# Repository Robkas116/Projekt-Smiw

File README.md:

This is a project of two-part PCB board based on STAMPS3 processor with 
  - RTC DS3231S with battery
  - TP4056 charger connected to USB port
  - Temperature, humidity and CO2 sensor SCD40-D-R1
  - FRAM 8KB memory MB85RS64V
  - Step Up MT3608
  - Step Down AMS1117-3.3

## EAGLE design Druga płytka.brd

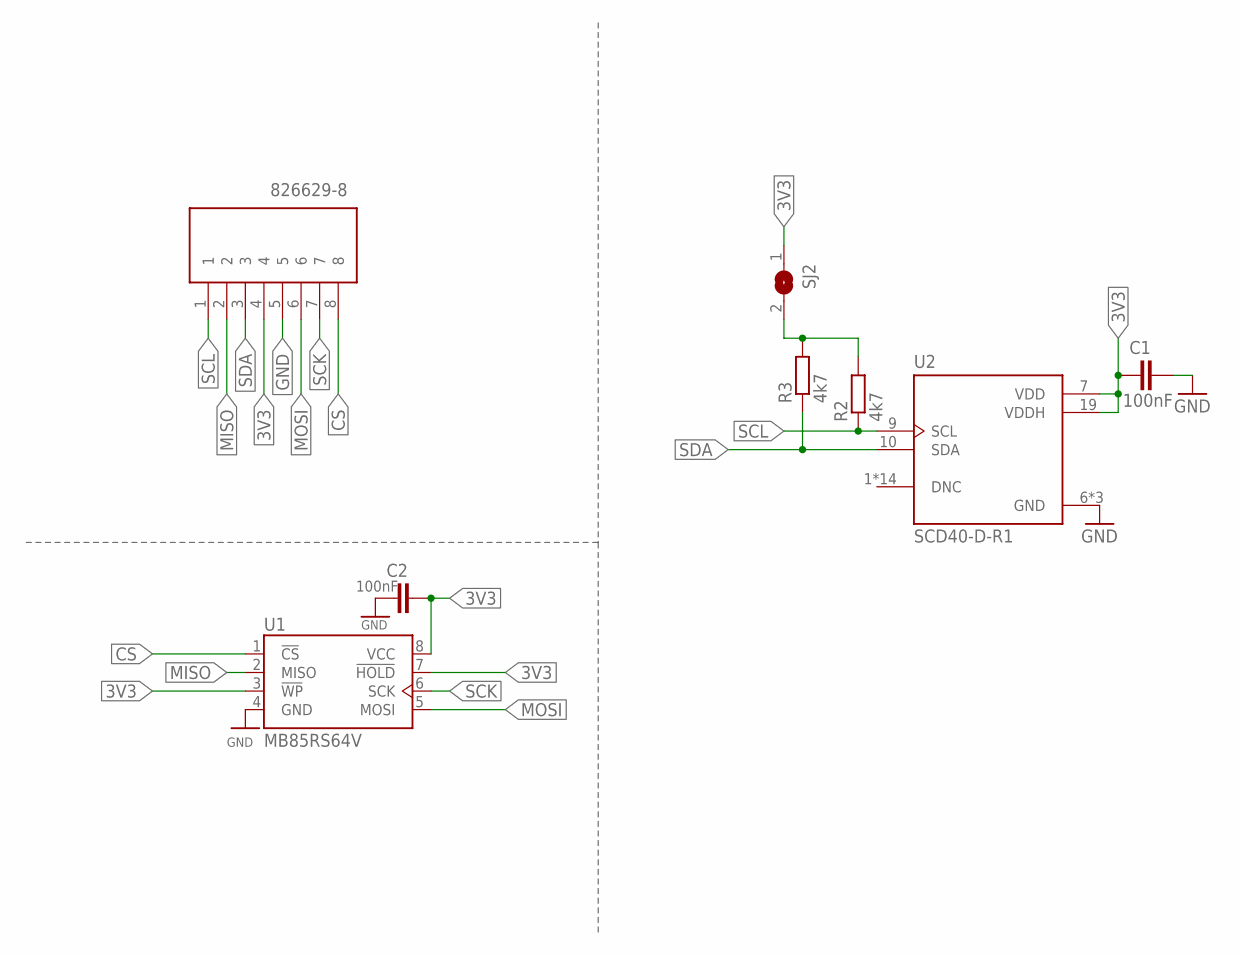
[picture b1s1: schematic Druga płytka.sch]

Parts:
C1, C2: 100nF; C0402
J1: 826629-8; HDRV8W63P0X254_1X8_2032X250X95
R2, R3: 4k7; R1206
SJ2: SJ
U1: MB85RS64V; SOIC127P600X155-8_R159_68_374R15
U2: SCD40-D-R1; XDCR_SCD40-D-R1

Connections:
3V3: C1.2, C2.1, J1.4, SJ2.1, U1.3 (!WP), U1.7 (!HOLD), U1.8 (VCC), U2.7 (VDD), U2.19 (VDDH)
CS: J1.8, U1.1 (!CS)
GND: C1.1, C2.2, J1.5, U1.4 (GND), U2.6 (GND), U2.20 (GND), U2.21 (GND)
JUMPER: R2.2, R3.2, SJ2.2
MISO: J1.2, U1.2 (MISO)
MOSI: J1.6, U1.5 (MOSI)
SCK: J1.7, U1.6 (SCK)
SCL: J1.1, R2.1, U2.9 (SCL)
SDA: J1.3, R3.1, U2.10 (SDA)

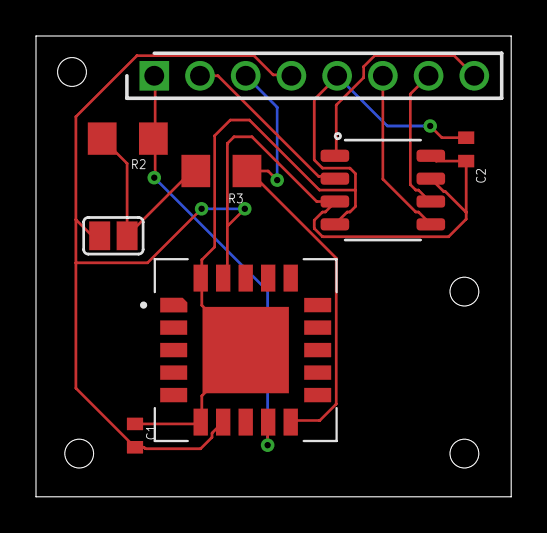
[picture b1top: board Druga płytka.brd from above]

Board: 2 copper layers, 26.4 x 25.6 mm, 8 parts (0 on the bottom side), 9 nets.

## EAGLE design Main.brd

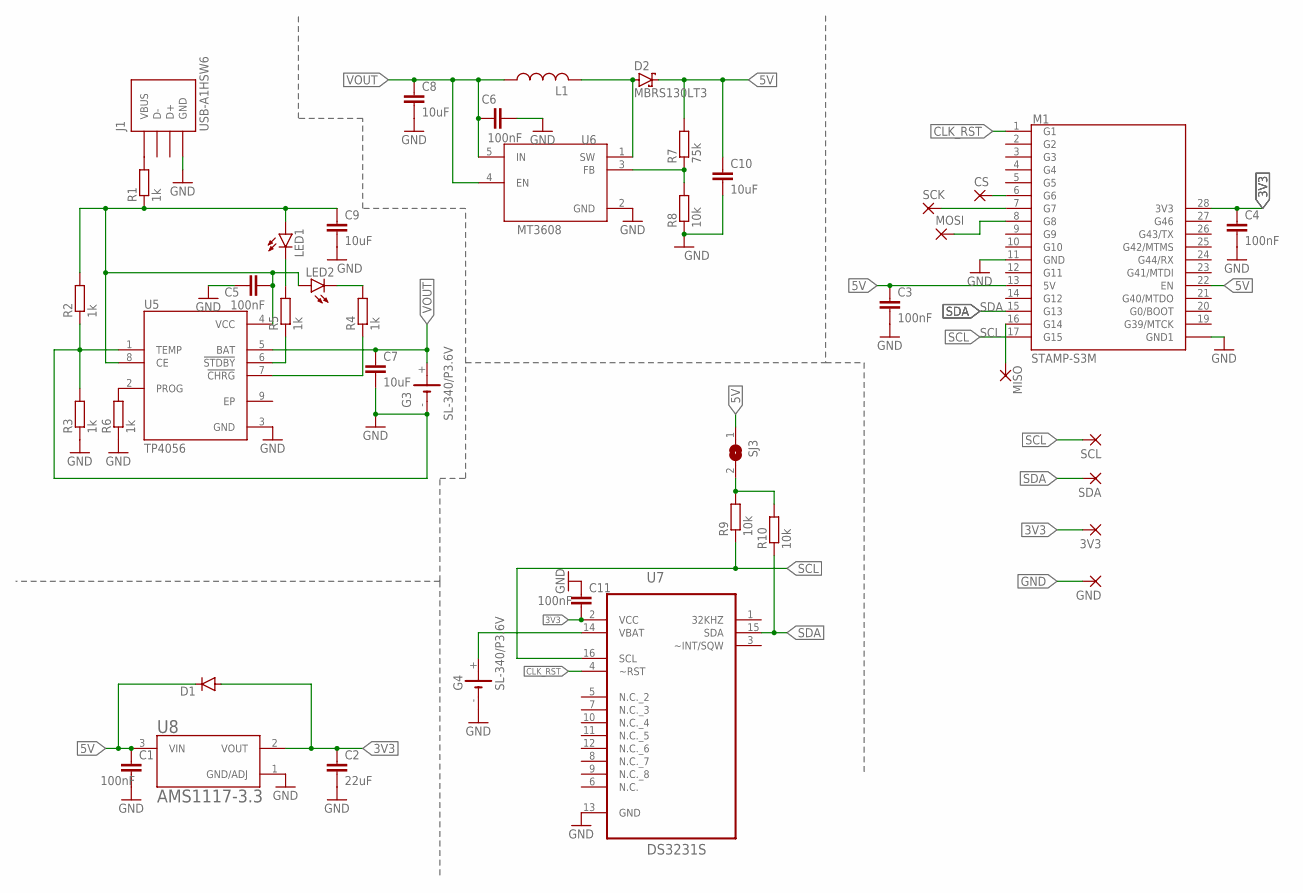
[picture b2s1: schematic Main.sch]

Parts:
3V3: 1,6/0,8
C1, C3, C4, C5, C6, C11: 100nF; C0402
C2: 22uF; C0402
C7, C8, C9, C10: 10uF; C0402
CS: 1,6/0,8
D1: DIODE-SMB; SMB
D2: MBRS130LT3; SMB
G3, G4: SL-340/P3.6V
GND: 1,6/0,8
J1: USB-A1HSW6; OST_USB-A1HSW6
L1: L-USL3225M; L3225M
LED1, LED2: LEDCHIPLED_0805; CHIPLED_0805
MISO: 1,6/0,8
MOSI: 1,6/0,8
R1, R2, R3, R4, R5, R6: 1k; M1206
R7: 75k; M1206
R8, R9, R10: 10k; M1206
SCK: 1,6/0,8
SCL: 1,6/0,8
SDA: 1,6/0,8
SJ3: SJ
U5: TP4056; SOP127P600X175-9N
U6: MT3608; SOT95P280X145-6N
U7: DS3231S; SOIC127P1032X265-16N
U8: AMS1117-3.3; SOT229P700X180-4N
U$1: STAMP-S3M-PIN; STAMPS3_PIN_FTP

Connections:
3V3: 3V3.1, C2.1, C4.1, C11.2, D1.A, U7.2 (VCC), U8.2 (VOUT), U$1.28 (3V3)
5V: C1.1, C3.1, C10.1, D1.C, D2.C, R7.2, SJ3.1, U8.3 (VIN), U$1.13 (5V), U$1.22 (EN)
CHRG: R4.1, U5.7 (!CHRG)
CHRG2: LED2.C, R4.2
CLK_RST: U7.4 (~RST), U$1.1 (G1)
CS: CS.1, U$1.6 (G6)
FB: R7.1, R8.2, U6.3 (FB)
GND: C1.2, C2.2, C3.2, C4.2, C5.1, C6.2, C7.2, C8.2, C9.2, C10.2, C11.1, G3.-, G4.-, GND.1, J1.4 (GND), R2.1, R3.1, R3.2, R6.1, R8.1, U5.1 (TEMP), U5.3 (GND), U6.2 (GND), U7.13 (GND), U8.1 (GND/ADJ), U$1.11 (GND), U$1.18 (GND1)
JUMPER: R9.2, R10.2, SJ3.2
MISO: MISO.1, U$1.16 (G14)
MOSI: MOSI.1, U$1.8 (G8)
unnamed: R6.2, U5.2 (PROG)
unnamed: LED1.C, R5.2
unnamed: J1.1 (VBUS), R1.2
SCK: SCK.1, U$1.7 (G7)
SCL: R9.1, SCL.1, U7.16 (SCL), U$1.17 (G15)
SDA: R10.1, SDA.1, U7.15 (SDA), U$1.15 (G13)
STDBY: R5.1, U5.6 (!STDBY)
SW: D2.A, L1.2, U6.1 (SW)
USB1: C5.2, C9.1, LED1.A, LED2.A, R1.1, R2.2, U5.4 (VCC), U5.8 (CE)
VBAT: G4.+, U7.14 (VBAT)
VOUT: C6.1, C7.1, C8.1, G3.+, L1.1, U5.5 (BAT), U6.4 (EN), U6.5 (IN)

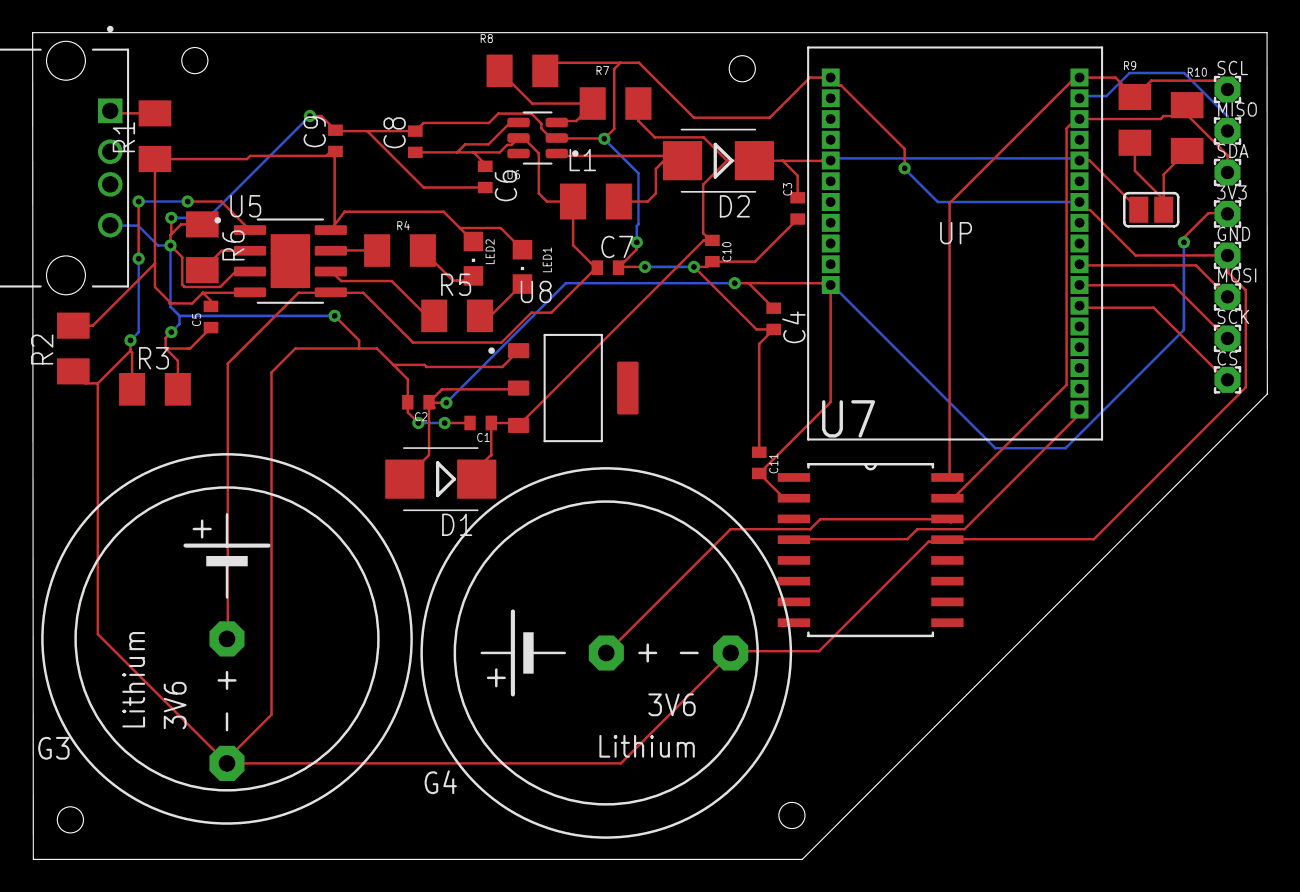
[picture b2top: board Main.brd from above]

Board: 2 copper layers, 75.6 x 50.6 mm, 43 parts (0 on the bottom side), 22 nets.

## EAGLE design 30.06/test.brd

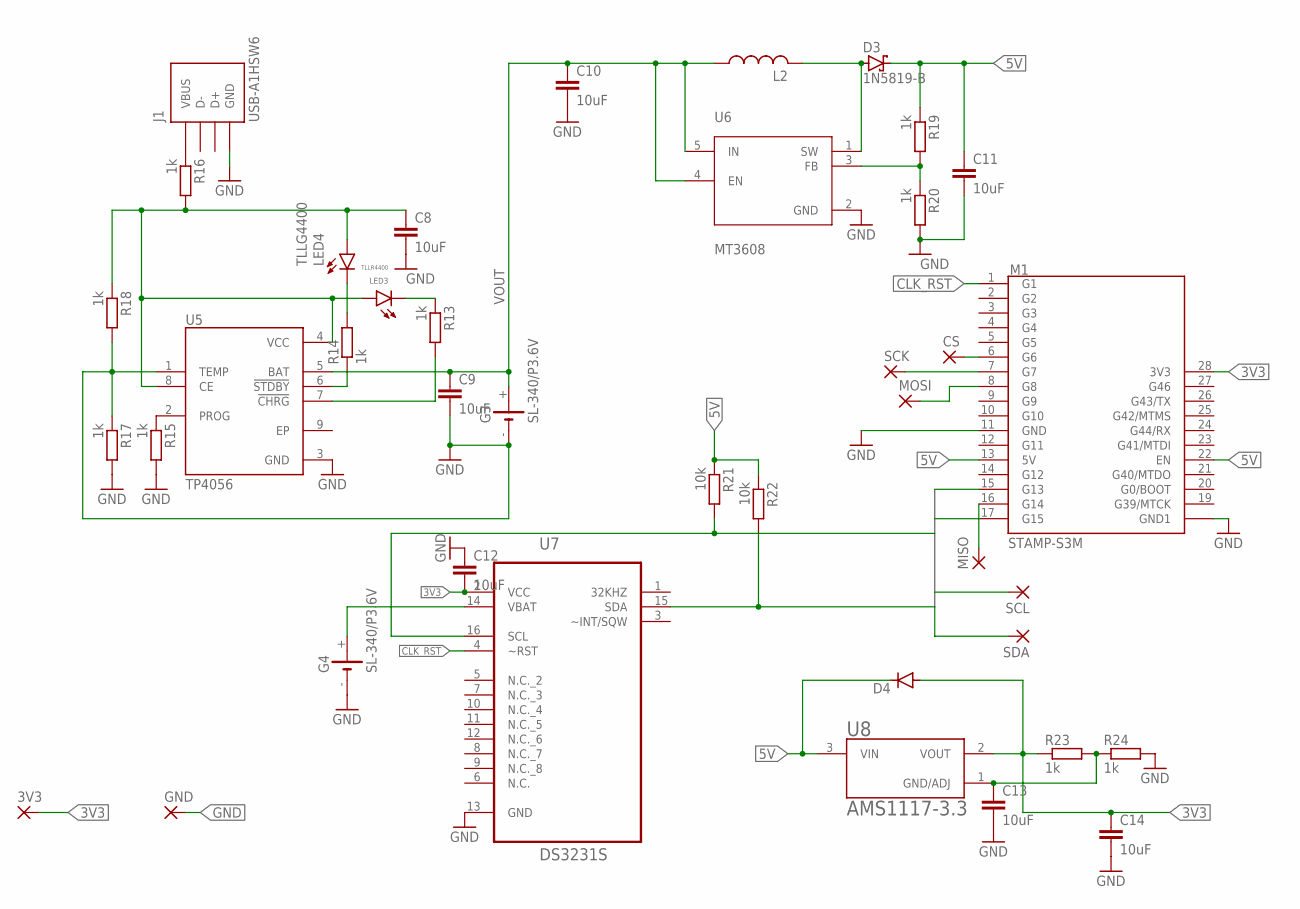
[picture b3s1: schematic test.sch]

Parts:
3V3: 1,6/0,8
C8, C9, C10, C11, C12, C13, C14: 10uF; C2.5-3
CS: 1,6/0,8
D3: 1N5819-B; DO41-7.6
D4: DIODE-D-2.5; D-2.5
G3, G4: SL-340/P3.6V
GND: 1,6/0,8
J1: USB-A1HSW6; OST_USB-A1HSW6
L2: L-US0204/7; 0204/7
LED3: TLLR4400; LED3MM
LED4: TLLG4400; LED3MM
MISO: 1,6/0,8
MOSI: 1,6/0,8
R13, R14, R15, R16, R17, R18, R19, R20, R23, R24: 1k; 0204V
R21, R22: 10k; 0204V
SCK: 1,6/0,8
SCL: 1,6/0,8
SDA: 1,6/0,8
U5: TP4056; SOP127P600X175-9N
U6: MT3608; SOT95P280X145-6N
U7: DS3231S; SOIC127P1032X265-16N
U8: AMS1117-3.3; SOT229P700X180-4N
U$1: STAMP-S3M-PIN; STAMPS3_PIN_FTP

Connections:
3V3: 3V3.1, C12.2, C14.1, D4.A, R23.1, U7.2 (VCC), U8.2 (VOUT), U$1.28 (3V3)
5V: C11.1, D3.C, D4.C, R19.1, R21.1, R22.1, U8.3 (VIN), U$1.13 (5V), U$1.22 (EN)
CHRG: R13.2, U5.7 (!CHRG)
CLK_RST: U7.4 (~RST), U$1.1 (G1)
CS: CS.1, U$1.6 (G6)
FB: R19.2, R20.1, U6.3 (FB)
GND: C8.2, C9.2, C10.2, C11.2, C12.1, C13.2, C14.2, G3.-, G4.-, GND.1, J1.4 (GND), R15.2, R17.1, R17.2, R18.2, R20.2, R24.2, U5.1 (TEMP), U5.3 (GND), U6.2 (GND), U7.13 (GND), U$1.11 (GND), U$1.18 (GND1)
MISO: MISO.1, U$1.16 (G14)
MOSI: MOSI.1, U$1.8 (G8)
unnamed: R15.1, U5.2 (PROG)
unnamed: LED4.K (C), R14.2
unnamed: LED3.K (C), R13.1
unnamed: C13.1, R23.2, R24.1, U8.1 (GND/ADJ)
SCK: SCK.1, U$1.7 (G7)
SCL: R21.2, SCL.1, U7.16 (SCL), U$1.17 (G15)
SDA: R22.2, SDA.1, U7.15 (SDA), U$1.15 (G13)
STDBY: R14.1, U5.6 (!STDBY)
SW: D3.A, L2.2, U6.1 (SW)
USB1: C8.1, J1.1 (VBUS), LED3.A, LED4.A, R16.1, R16.2, R18.1, U5.4 (VCC), U5.8 (CE)
VBAT: G4.+, U7.14 (VBAT)
VOUT: C9.1, C10.1, G3.+, L2.1, U5.5 (BAT), U6.4 (EN), U6.5 (IN)

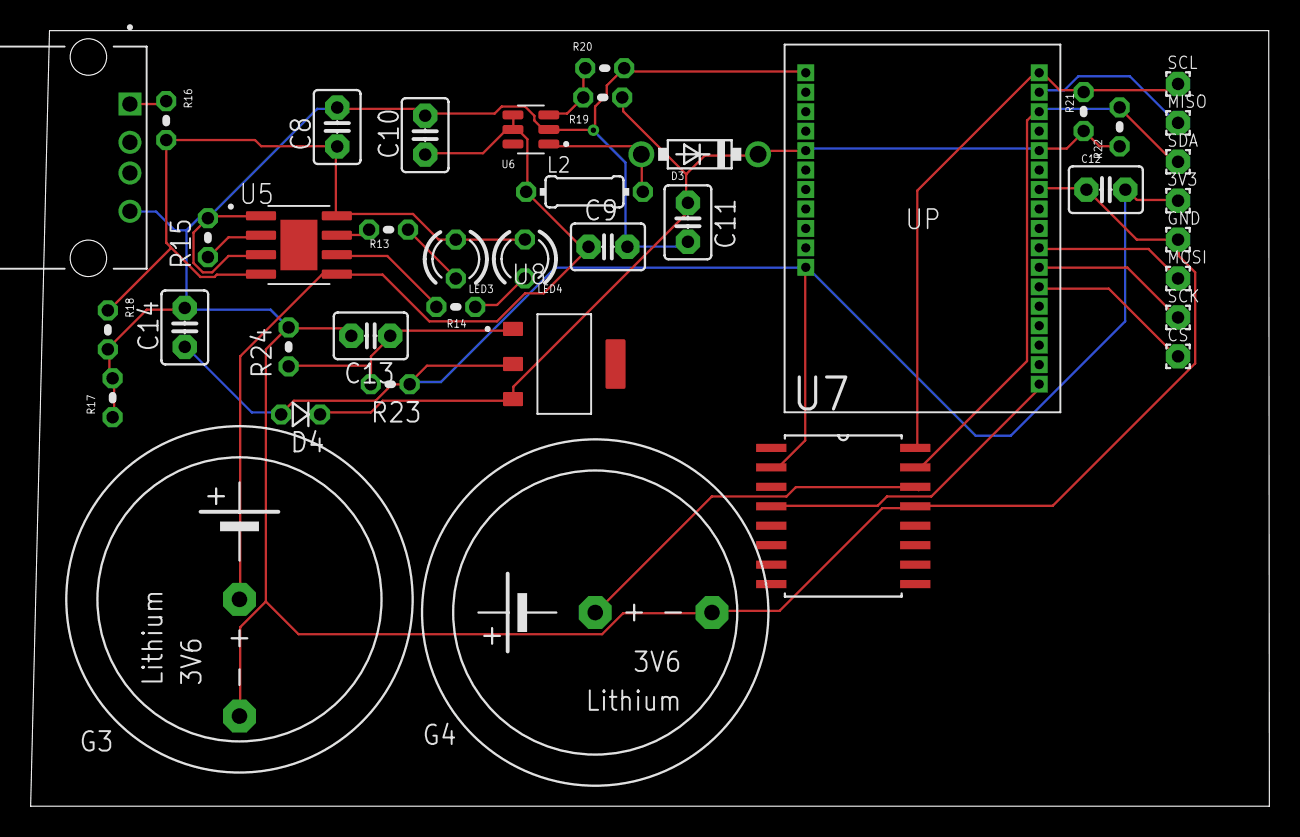
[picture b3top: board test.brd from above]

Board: 2 copper layers, 80.8 x 50.6 mm, 40 parts (0 on the bottom side), 21 nets.

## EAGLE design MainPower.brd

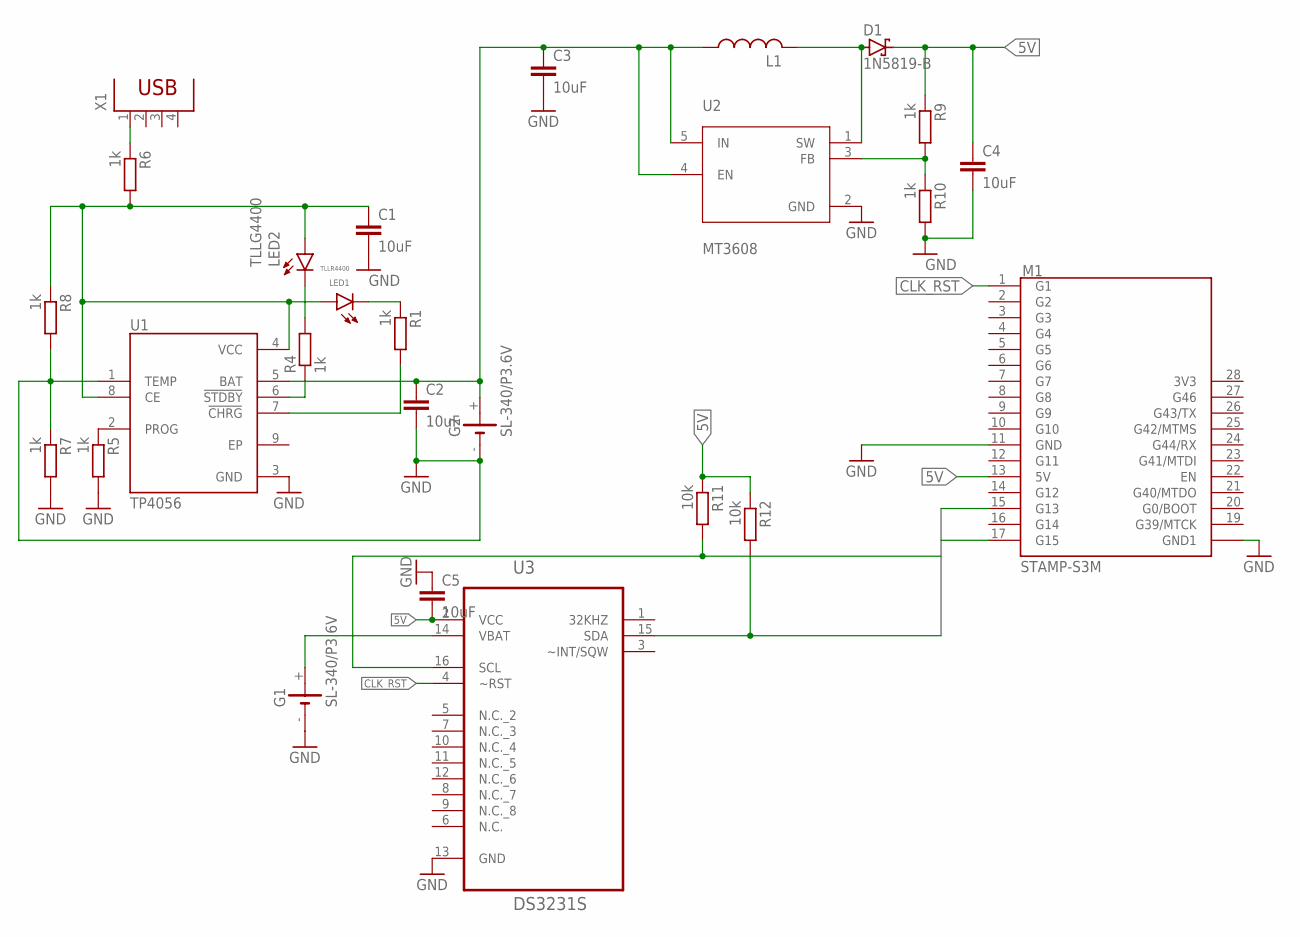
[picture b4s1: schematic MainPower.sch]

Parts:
C1, C2, C3, C4, C5: 10uF; C2.5-3
D1: 1N5819-B; DO41-7.6
G1, G2: SL-340/P3.6V
L1: L-US0204/7; 0204/7
LED1: TLLR4400; LED3MM
LED2: TLLG4400; LED3MM
R1, R4, R5, R6, R7, R8, R9, R10: 1k; 0204V
R11, R12: 10k; 0204V
U1: TP4056; SOP127P600X175-9N
U2: MT3608; SOT95P280X145-6N
U3: DS3231S; SOIC127P1032X265-16N
U$2: STAMP-S3M-PIN; STAMPS3_PIN_FTP
X1: PN61729

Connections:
3V3: U$2.28 (3V3)
5V: C4.1, C5.2, D1.C, R9.1, R11.1, R12.1, U3.2 (VCC), U$2.13 (5V)
CLK_RST: U3.4 (~RST), U$2.1 (G1)
GND: C1.2, C2.2, C3.2, C4.2, C5.1, G1.-, G2.-, R5.2, R7.1, R7.2, R8.2, R10.2, U1.1 (TEMP), U1.3 (GND), U2.2 (GND), U3.13 (GND), U$2.11 (GND), U$2.18 (GND1)
unnamed: D1.A, L1.2, U2.1 (SW)
unnamed: R4.1, U1.6 (!STDBY)
unnamed: G1.+, U3.14 (VBAT)
unnamed: R5.1, U1.2 (PROG)
unnamed: LED2.K (C), R4.2
unnamed: LED1.K (C), R1.1
unnamed: R1.2, U1.7 (!CHRG)
unnamed: C2.1, C3.1, G2.+, L1.1, U1.5 (BAT), U2.4 (EN), U2.5 (IN)
unnamed: R9.2, R10.1, U2.3 (FB)
SCL: R11.2, U3.16 (SCL), U$2.17 (G15)
SDA: R12.2, U3.15 (SDA), U$2.15 (G13)
USB: C1.1, LED1.A, LED2.A, R6.1, R6.2, R8.1, U1.4 (VCC), U1.8 (CE), X1.1

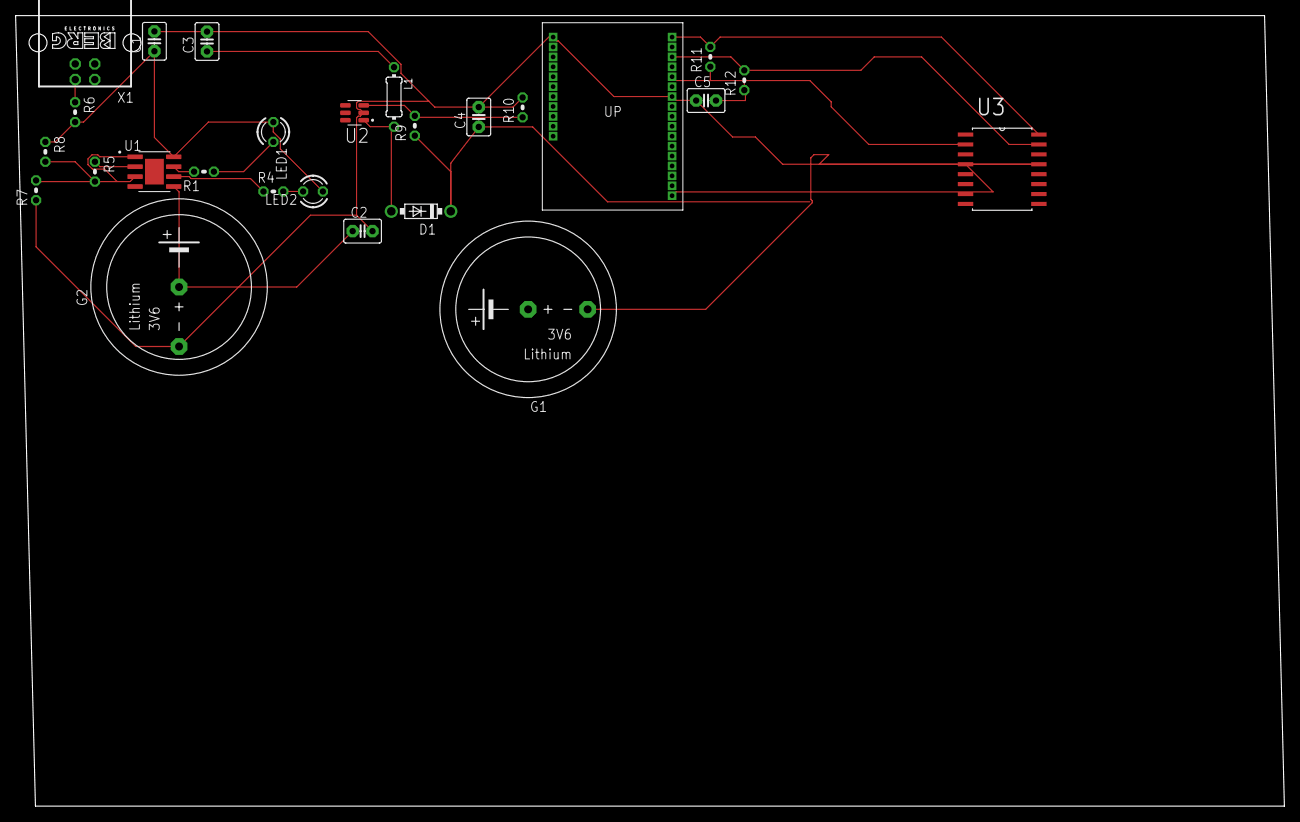
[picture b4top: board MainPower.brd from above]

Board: 2 copper layers, 162.5 x 101.3 mm, 26 parts (0 on the bottom side), 15 nets.

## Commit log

2026-06-11 Add final project of PCB boards and cleaning repository up
2026-06-11 Add project description to README.md
